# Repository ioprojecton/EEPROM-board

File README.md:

I2C EEPROM memory expansion board

EEPROM board is designed for usage with various development systems and other MCU device with I2C protocol. EEPROM accessory board is designed to add 4 x 24LCxx family of EEPROM memory to a microcontroller via serial I2C communication.

EEPROM Board is the perfect solution for adding or increasing the available EEPROM storage area for your system. This board adds four 24Lxx EEPROM's to a standard I2C bus. 

Data is transferred serially using this protocol. Data is stored permanently in these devices, even with the power disconnected. 

Key features:
•DIP sockets for easy installation of EEPROM memory chips.
•Predefined and printed on board addresses for sockets.
•400Khz speed guaranteed (look datasheet for speed of your EEPROM chip).
•Only 2 data lines are required for control and storage using the standard I2C bus arrangement.
•Decoupling capacitors are also included onboard for each IC.

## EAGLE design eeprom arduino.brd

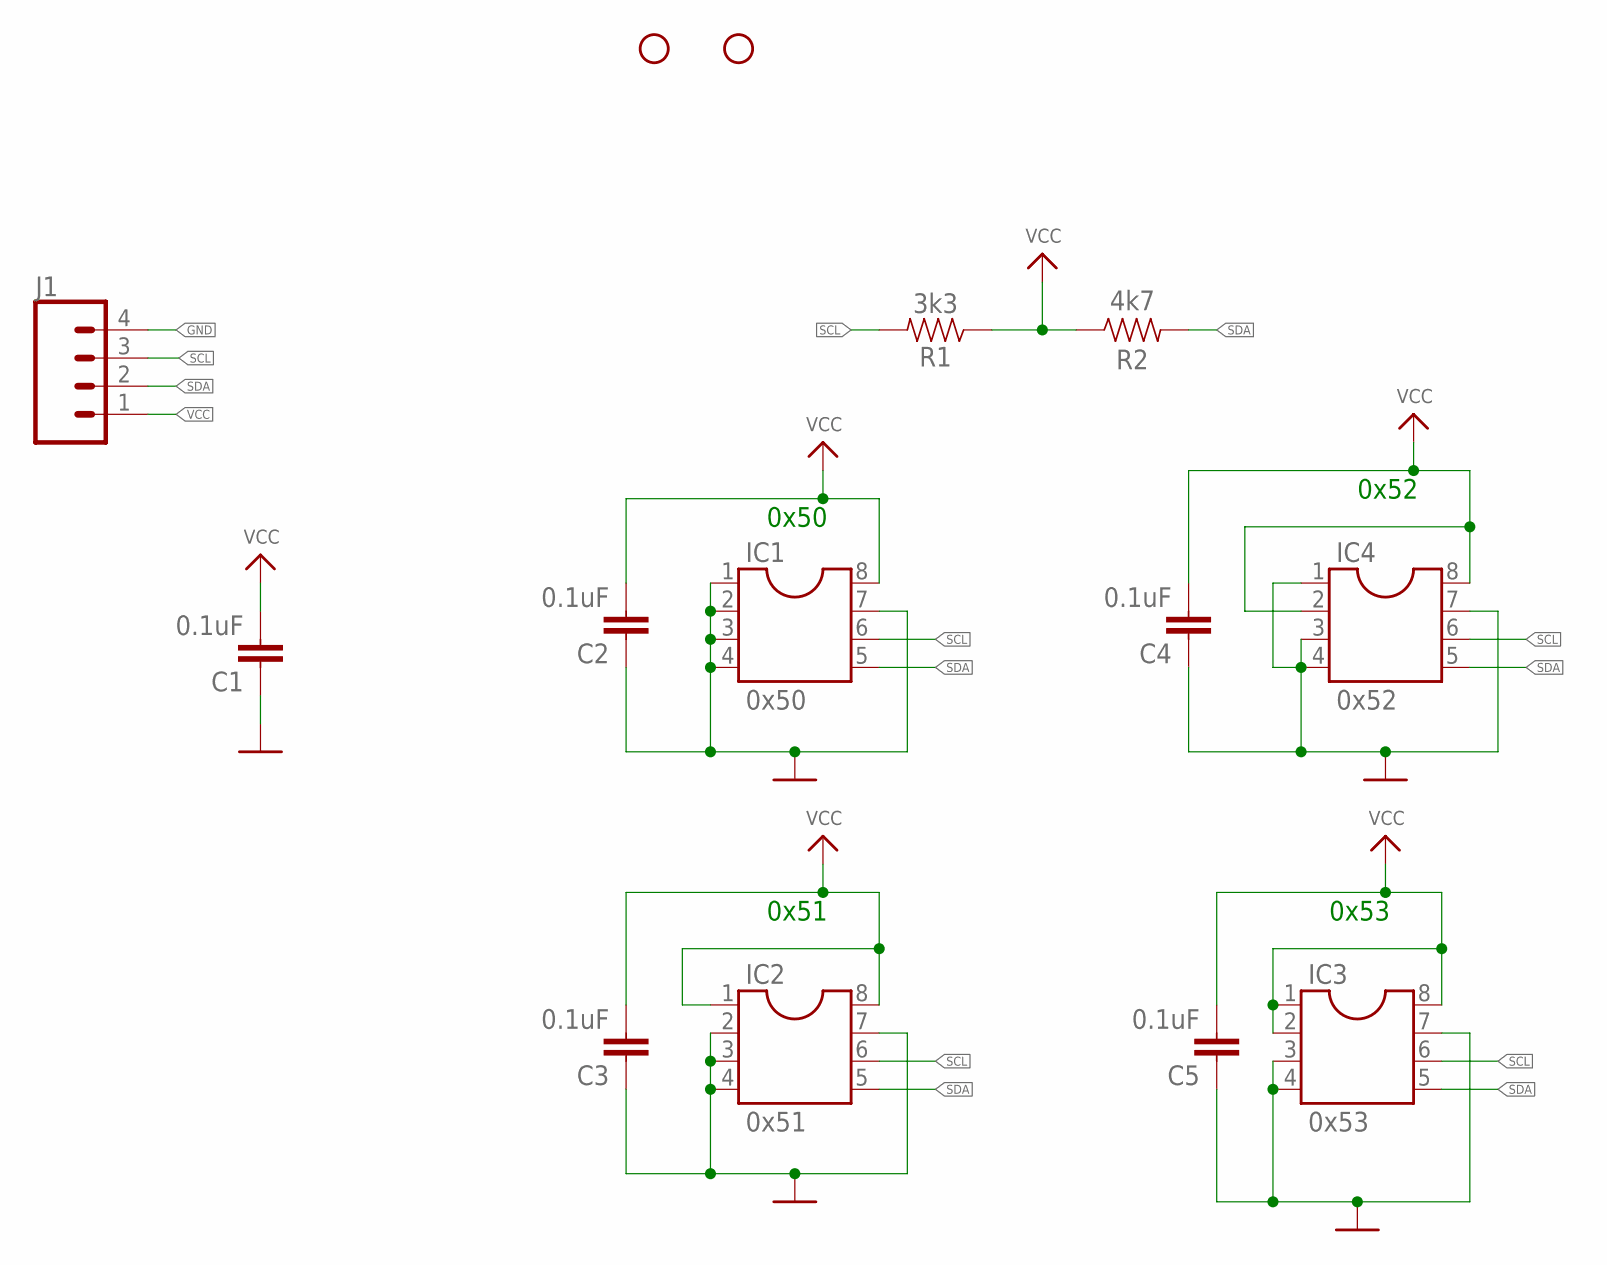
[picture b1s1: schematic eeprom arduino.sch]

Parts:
C1, C2, C3, C4, C5: 0.1uF; CAP-PTH-SMALL-KIT
H1, H2: STAND-OFF
IC1: 0x50; SOCKET-08
IC2: 0x51; SOCKET-08
IC3: 0x53; SOCKET-08
IC4: 0x52; SOCKET-08
J1: CONN_04POLAR; MOLEX-1X4
R1: 3k3; AXIAL-0.3
R2: 4k7; AXIAL-0.3

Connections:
GND: C1.1, C2.1, C3.1, C4.1, C5.1, IC1.1, IC1.2, IC1.3, IC1.4, IC1.7, IC2.2, IC2.3, IC2.4, IC2.7, IC3.3, IC3.4, IC3.7, IC4.1, IC4.3, IC4.4, IC4.7, J1.4
SCL: IC1.6, IC2.6, IC3.6, IC4.6, J1.3, R1.P$2 (2)
SDA: IC1.5, IC2.5, IC3.5, IC4.5, J1.2, R2.P$2 (2)
VCC: C1.2, C2.2, C3.2, C4.2, C5.2, IC1.8, IC2.1, IC2.8, IC3.1, IC3.2, IC3.8, IC4.2, IC4.8, J1.1, R1.P$1 (1), R2.P$1 (1)

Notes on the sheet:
0x50
0x51
0x52
0x53

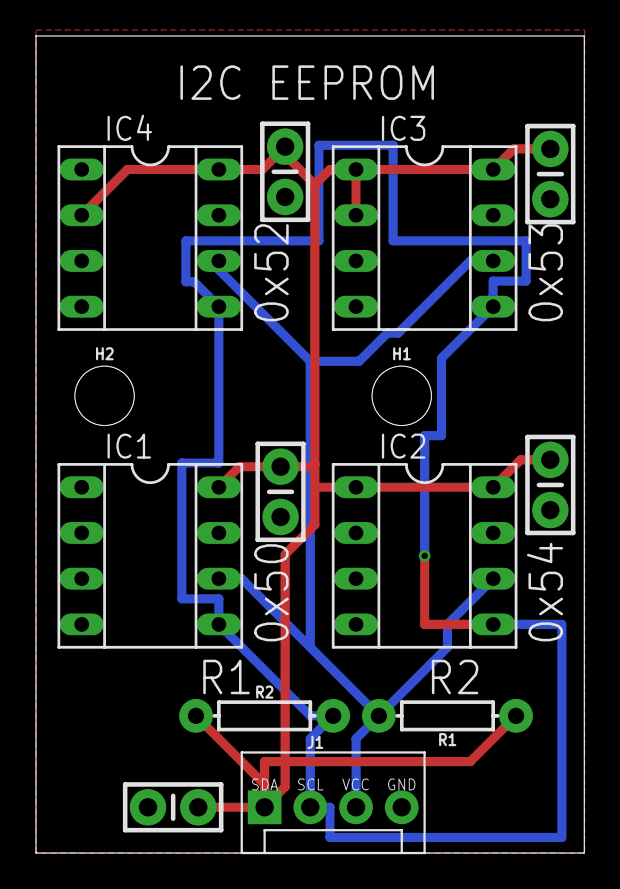
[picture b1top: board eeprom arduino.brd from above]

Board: 2 copper layers, 30.5 x 45.4 mm, 14 parts (0 on the bottom side), 4 nets.

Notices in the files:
parts and their libraries:
SparkFun-Capacitors: Licensing: Creative Commons ShareAlike 4.0 International - https://creativecommons.org/licenses/by-sa/4.0
